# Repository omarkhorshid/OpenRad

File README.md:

# OpenRad
Introducing OpenRad, a simple radiation monitoring solution powered by the SBM-20 GM tube and TTGO ESP32 microcontroller. this project offers a user-friendly approach to tracking and measuring radiation levels.

# Table of Contents
- [Demo](#demo)
- [Install](#install)
- [Folder Structure](#folder-structure)
- [FAQS](#faqs)
- [License](#license)

# Demo
### Device UI

### Youtube Demo

# Install
1. Install [VSCode](https://code.visualstudio.com/).
2. Install [PlatformIO](https://platformio.org/).
3. Clone this repository 
```bash
git clone https://github.com/omarkhorshid/OpenRad.git
```
4. (optional) Install [Squareline Studio](https://squareline.io/).
5. (optional) For Squareline, Change the project settings save paths to match your project directory.
6. In PlatformIO extension: Platform > Upload the Filesystem Image.
7. In PlatformIO extension: General > Upload the code to the TTGO board.

# Dependencies
- [lvgl v8.3.11](https://github.com/lvgl/lvgl/tree/release/v8.3)
- [TFT_eSPI v2.4.61](https://github.com/Bodmer/TFT_eSPI)
- [AsyncTCP-esphome v1.2.2](https://github.com/esphome/AsyncTCP.git)
- [ESPAsyncWebServer-esphome v2.1.0](https://github.com/esphome/ESPAsyncWebServer.git)
- [PubSubClient v2.8](https://github.com/knolleary/pubsubclient.git)
- [ArduinoJson v7.0.4](https://github.com/bblanchon/ArduinoJson.git)

# Folder Structure
### Software/Firmware/src
- `hardware.cpp/h` : Contains hardware init and functions. 
- `settings.cpp/h` : Contains the settings.
- `geiger.cpp/h` : Contains geiger calculations.
- `gui.cpp/h` : Contains LVGL functions.
- `connectivity.cpp/h` : Contains all the connectivity functions.

### Software/Firmware/lib/ui/src
- `ui_events.c/h` : Contains the UI events.

### Software/Firmware/data
- `index.html` : Contains the web interface.
- `chart.js` : Chart.js Library file.

# Schematics

[View project schematics](./Hardware/Schematics.pdf)

# FAQs
### How do I Navigate the UI in OpenRad?
Using the three buttons, up down and enter. ...

### How do I change the measuring window?
After uploading the code to the ESP, open the settings cogwheel, and change the settings you want.

### How do I turn OpenRad off?
- For **Sleep mode**: Navigate to the power button and click it.
- For **Deep Sleep mode**: Hold the button untill this message pops up, then release it before it disappears.

### What types of connectivity does OpenRad have?
OpenRad has WiFi and MQTT connectivity to be able to remotely monitor the radiation levels from the Web interface.

### How do I connect to OpenRad?
To connect to OpenRad and access the web interface:

If not connected to a Wifi network:
1. Enable Wifi from the on device settings
2. Enable "Wi-Fi Access Point"
3. Connect to the device's AP using the password on screen
4. Navigate to "http://192.168.4.1" or use the "Manage Router" option on your phone

If Connected:
- From a device on the same network navigate to the IP address showing on the device screen in the Connectivity settings

### What are the Measurement Settings?
1. **Window Size:** Number of samples used to calculate the average radiation intensity.

- **Bigger** values help the device give a more stable reading and theoretically increse its precision, but it will react slowler to changes.
- **Smaller** values help the device react faster to changes, but the readings might fluctuate more and theoretically decrease the precision.

2. **Sampling Period**: This is how often the device takes a reading (e.g., every N milliseconds).
- **Bigger** values make the device take readings less frequently, reducing energy consumption during sleep, but the device will react slower to changes.
- **Smaller** values make the device take readings more often, making it quicker to detect changes, but the readings may be less precise and the device consumes more power during sleep (If sleep sampling is enabled).
# License
OpenRad is [BSD-3 Licensed](license.txt '3-Clause BSD License')

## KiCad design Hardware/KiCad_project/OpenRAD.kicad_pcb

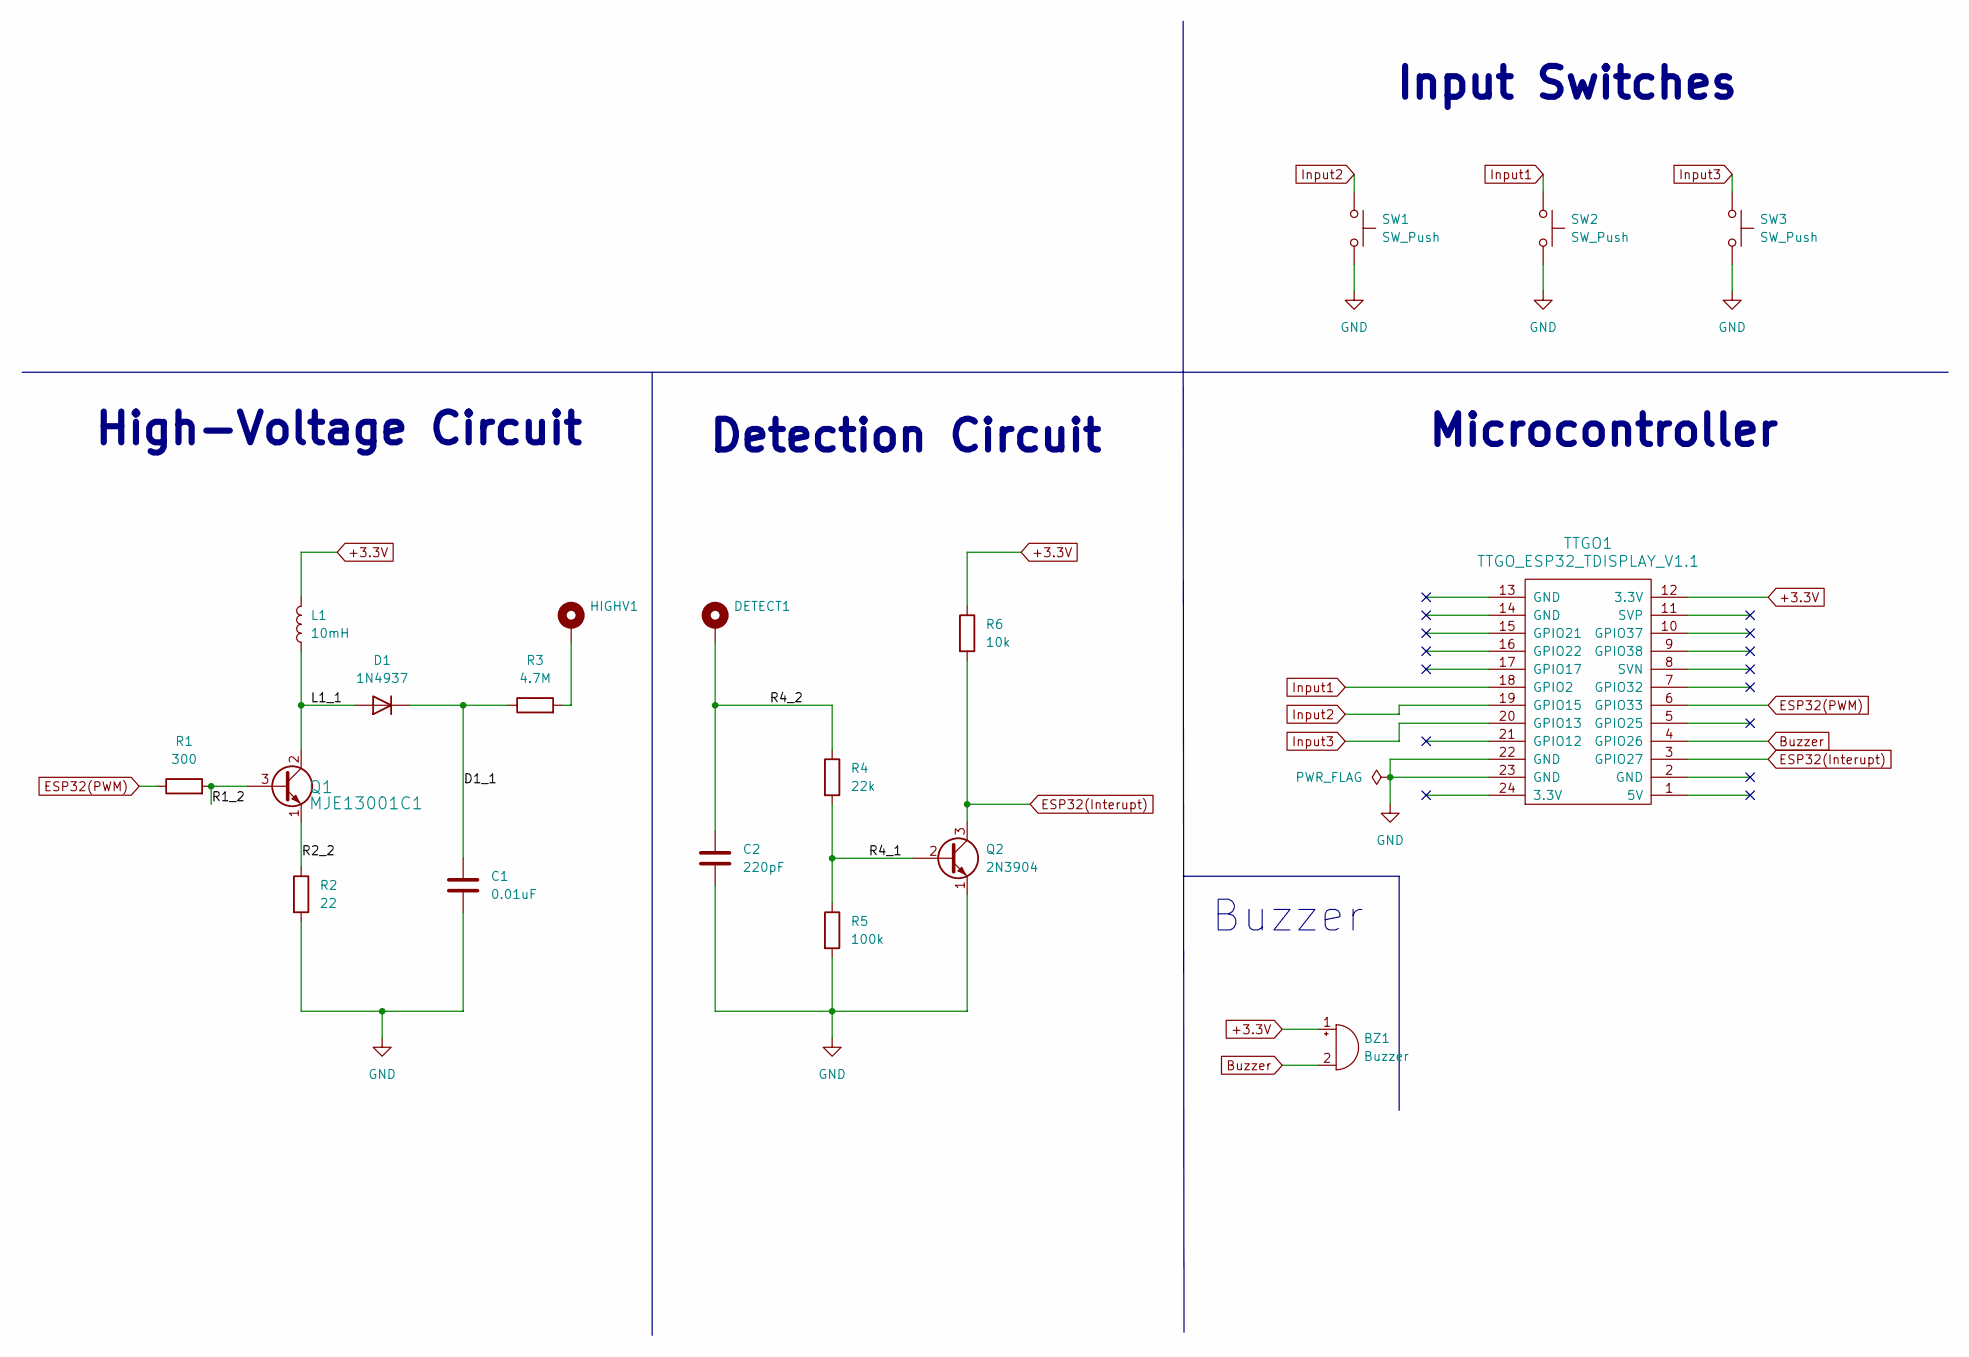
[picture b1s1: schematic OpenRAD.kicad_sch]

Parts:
BZ1: Buzzer; Buzzer_12x9.5RM7.6
C1: 0.01uF; C_Rect_L18.0mm_W5.0mm_P15.00mm_FKS3_FKP3
C2: 220pF; C_Rect_L18.0mm_W5.0mm_P15.00mm_FKS3_FKP3
D1: 1N4937; D_DO-41_SOD81_P10.16mm_Horizontal
DETECT1: DETECT; PAD_7X4
HIGHV1: HIGHV; PAD_7X4
L1: 10mH; L_Axial_L14.0mm_D4.5mm_P15.24mm_Horizontal_Fastron_LACC
Q1: MJE13001C1; TO-92_Inline
Q2: 2N3904; TO-92_Inline
R1: 300; R_Axial_DIN0207_L6.3mm_D2.5mm_P10.16mm_Horizontal
R2: 22; R_Axial_DIN0207_L6.3mm_D2.5mm_P10.16mm_Horizontal
R3: 4.7M; R_Axial_DIN0414_L11.9mm_D4.5mm_P15.24mm_Horizontal
R4: 22k; R_Axial_DIN0207_L6.3mm_D2.5mm_P10.16mm_Horizontal
R5: 100k; R_Axial_DIN0207_L6.3mm_D2.5mm_P10.16mm_Horizontal
R6: 10k; R_Axial_DIN0207_L6.3mm_D2.5mm_P10.16mm_Horizontal
SW1, SW2, SW3: SW_Push; SW_PUSH_6mm_H13mm
TTGO1: TTGO_ESP32_TDISPLAY_V1.1; TTGO_ESP32_TDisplay_v1.1

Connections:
+3.3V: BZ1.1 (+), L1.2, R6.1, TTGO1.12 (3.3V)
/D1_1: C1.1, D1.1 (K), R3.1
/L1_1: D1.2 (A), L1.1, Q1.2 (C)
/R1_2: Q1.3 (B), R1.2
/R2_2: Q1.1 (E), R2.1
/R4_1: Q2.2 (B), R4.2, R5.1
/R4_2: C2.1, DETECT1.1, R4.1
Buzzer: BZ1.2 (-), TTGO1.4 (GPIO26)
ESP32(Interupt): Q2.3 (C), R6.2, TTGO1.3 (GPIO27)
ESP32(PWM): R1.1, TTGO1.6 (GPIO33)
GND: C1.2, C2.2, Q2.1 (E), R2.2, R5.2, SW1.2, SW2.2, SW3.2, TTGO1.22 (GND), TTGO1.23 (GND)
Input1: SW2.1, TTGO1.18 (GPIO2)
Input2: SW1.1, TTGO1.19 (GPIO15)
Input3: SW3.1, TTGO1.20 (GPIO13)
unnamed: HIGHV1.1, R3.2

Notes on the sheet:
Input Switches
Buzzer
Microcontroller
High-Voltage Circuit
Detection Circuit

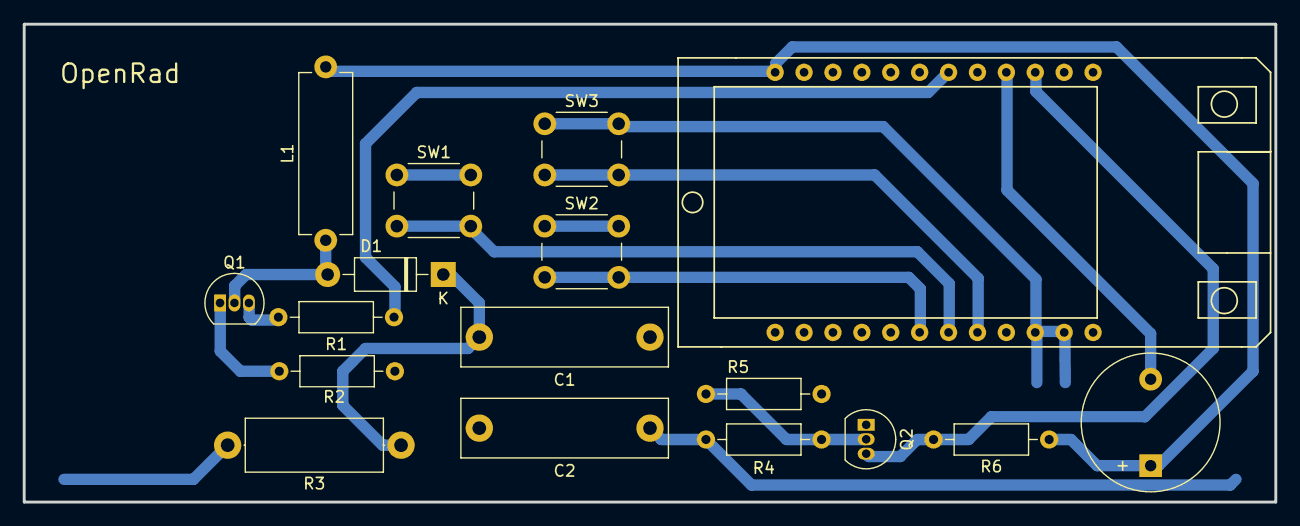
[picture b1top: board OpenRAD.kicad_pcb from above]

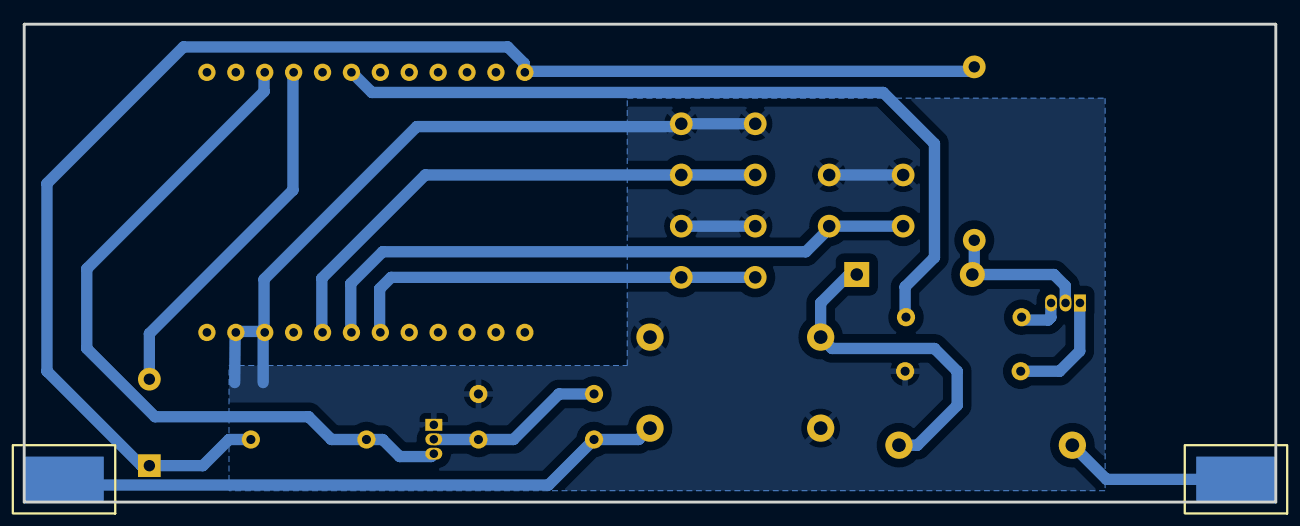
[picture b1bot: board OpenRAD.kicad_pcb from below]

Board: 2 copper layers, 110.0 x 42.0 mm, 19 parts (2 on the bottom side), 15 nets.

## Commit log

2024-04-26 v1 Commit
2024-04-26 Added demo
2024-04-26 Added Demos
2024-04-26 Update README.md
    should add more FAQs
2024-04-26 Readme edit
2024-04-26 Readme Update
2024-04-26 Added schematics PDF
2024-04-26 Added schematics
2024-04-30 Added Get_on_PCBWAY.png
2024-04-30 Update README with PCBWay PCB Link
2024-06-04 Added KiCad project files
2024-09-13 Fix bug #3
2024-09-14 MQTT Publish Interval #4
    + added mqtt_publish_interval to control the delay between mqtt messages.
2024-09-14 Changed mqtt_publish_interval to int #4
    *Fix type inconsistency by changing mqtt_publish_interval to int
2025-01-03 Adjustment to Measurement Settings #5
    In "Measurement Setting" in "Web UI":
    * Adjusted Unit for "Window Size".
    + Added placeholder text to "Window Size".
    * Adjusted both "Window Size" and "samplingPeriod" Unit Labels to bind to their respective text inputs.
    In Readme:
    + added "What are the Measurement Settings?" to FAQS.
2025-12-16 Added functionality of going to deep sleep when battery is 0%
